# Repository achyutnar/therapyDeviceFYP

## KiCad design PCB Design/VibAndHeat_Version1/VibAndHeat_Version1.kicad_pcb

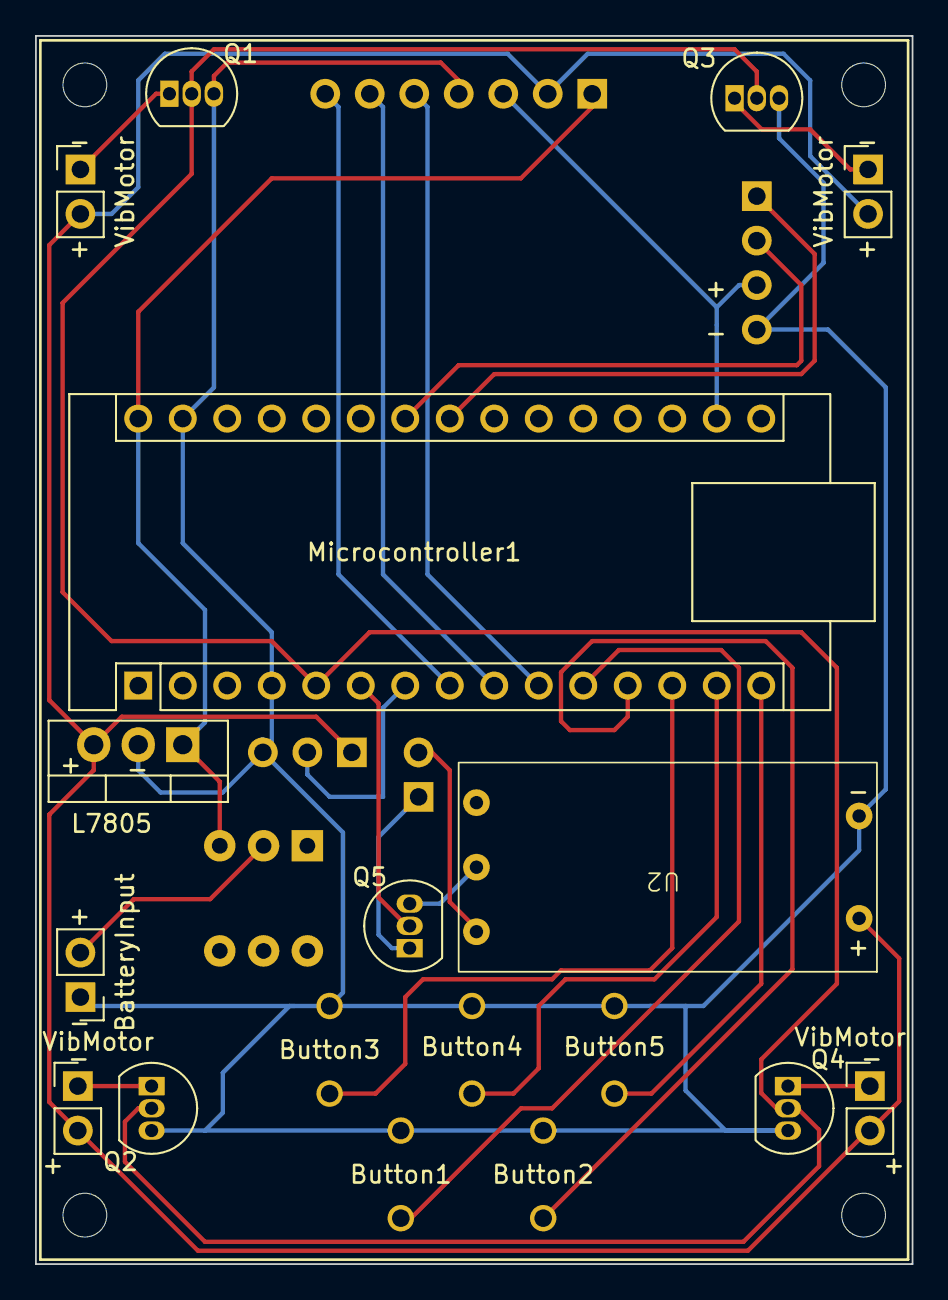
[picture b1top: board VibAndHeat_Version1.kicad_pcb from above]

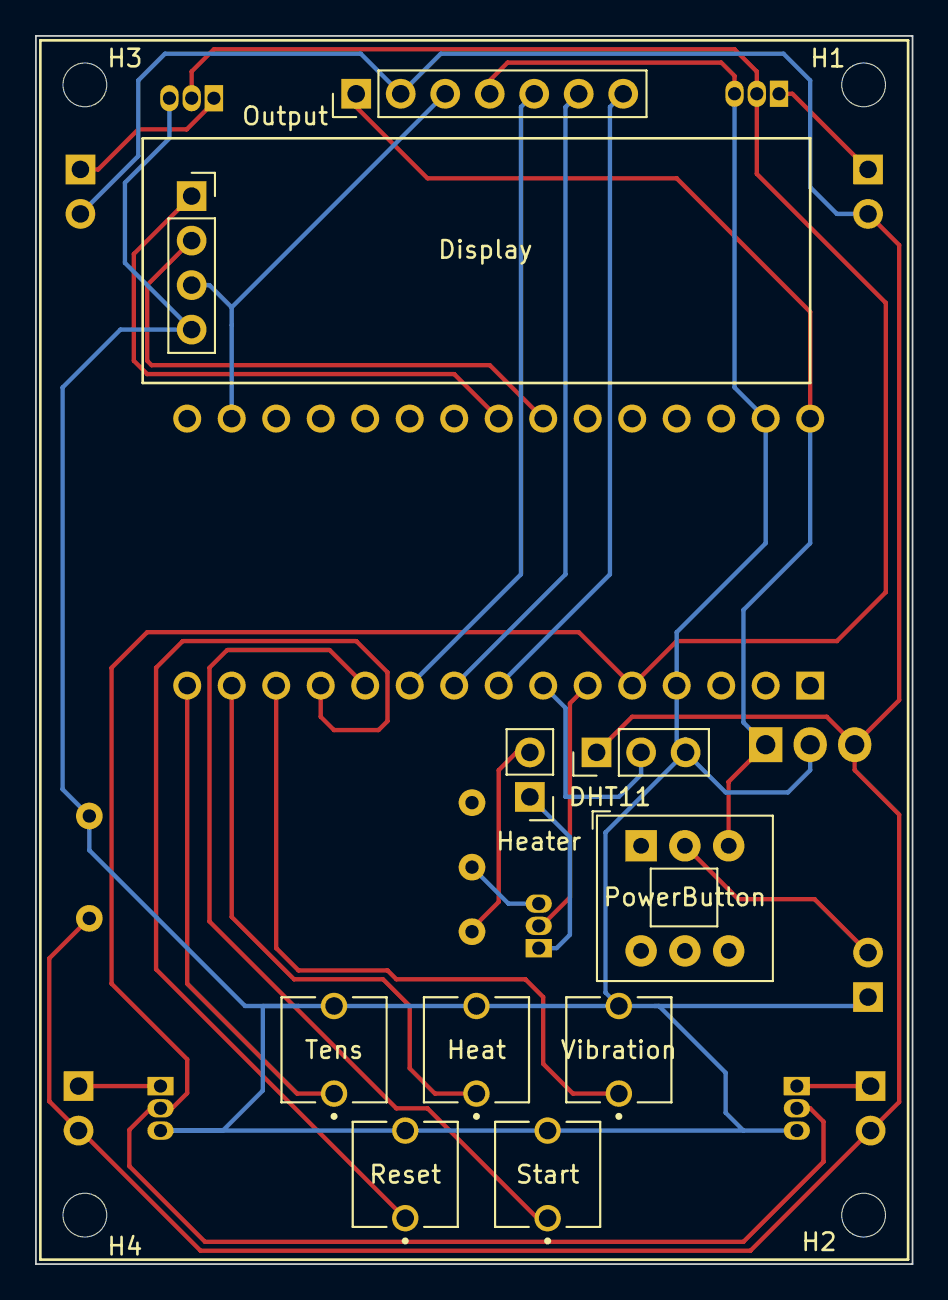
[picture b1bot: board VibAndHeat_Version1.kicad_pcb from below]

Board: 2 copper layers, 50.0 x 70.1 mm, 27 parts (14 on the bottom side), 25 nets.

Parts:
Button1: Start; Button_Push_2pin
Button2: Reset; Button_Push_2pin
Button3: Vibration; Button_Push_2pin
Button4: Heat; Button_Push_2pin
Button5: Tens; Button_Push_2pin
H1, H2, H3, H4: MountingHole; MountingHole_2.5mm
J1, J2, J3, J4: VibMotor; PinHeader_1x02_P2.54mm_Vertical
J5: Heater; PinHeader_1x02_P2.54mm_Vertical
J6: BatteryInput; PinHeader_1x02_P2.54mm_Vertical
J7: Display; PinSocket_1x04_P2.54mm_Vertical
J8: Output; PinHeader_1x07_P2.54mm_Vertical
Microcontroller1: Nano BLE33; Arduino_Nano
Q1, Q2, Q3, Q4, Q5: 2N2222; TO-92_Inline
SW1: PowerButton; SW_Push_2P2T_Toggle_CK_PVA2OAH5xxxxxxV2
U1: DHT11; PinHeader_1x03_P2.54mm_Vertical
U2: Step_up_Convertor_12v
U3: L7805; TO-220-3_Vertical

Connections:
GND: Button1.2, Button2.2, Button3.2, Button4.2, Button5.2, J6.1, J7.4, J8.4, Microcontroller1.4 (GND), Microcontroller1.29 (GND), Q1.3 (C), Q2.3 (C), Q3.3 (C), Q4.3 (C), U1.3 (GND), U2.2 (GND1), U3.2 (GND)
HT-Heater: Microcontroller1.6 (D3), Q5.2 (B)
HT-Sensor: Microcontroller1.7 (D4), U1.2 (IO)
Input_5v: J1.2, J2.2, J3.2, J4.2, J8.2, U1.1 (VCC), U2.1 (VIN), U3.3 (OUT)
Input_7v4: J8.1, Microcontroller1.30 (VIN), SW1.3 (C), U3.1 (IN)
unnamed: J1.1, Q1.1 (E)
unnamed: J2.1, Q2.1 (E)
unnamed: J3.1, Q3.1 (E)
unnamed: J4.1, Q4.1 (E)
unnamed: J5.1, Q5.1 (E)
unnamed: J5.2, U2.3 (VOUT+)
unnamed: J6.2, SW1.2 (B)
unnamed: Q5.3 (C), U2.4 (GND2)
Output-3v3: J7.3, J8.3, Microcontroller1.17 (3V3)
SCL_Display: J7.2, Microcontroller1.24 (A5)
SDA_Display: J7.1, Microcontroller1.23 (A4)
SW-Heat: Button4.1, Microcontroller1.14 (D11)
SW-Reset: Button2.1, Microcontroller1.12 (D9)
SW-Start: Button1.1, Microcontroller1.11 (D8)
SW-Tens: Button5.1, Microcontroller1.15 (D12)
SW-Vibration: Button3.1, Microcontroller1.13 (D10)
TT-Enable: J8.7, Microcontroller1.8 (D5)
TT-Input1: J8.6, Microcontroller1.9 (D6)
TT-Input2: J8.5, Microcontroller1.10 (D7)
VT-Motor: Microcontroller1.5 (D2), Q1.2 (B), Q2.2 (B), Q3.2 (B), Q4.2 (B)

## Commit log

2025-05-12 Files added
2025-05-13 Component Dimension file added
